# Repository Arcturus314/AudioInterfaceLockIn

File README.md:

A basic dual-phase lockin implementation for a 2in/2out sound card or audio interface using pyaudio. Tested on a MOTU M2 at 32bits/48kHz sample rate under ALSA.

Connect CH1 OUT to CH1 IN through a loopback wire and set gains appropriately. CH2 OUT should be the input to the DUT and CH2 IN should be the output of the DUT.

Example output file is `log_movemic.txt`. This was a simple experiment in which CH2 OUT was connected to a speaker, and CH2 IN connected to a microphone. The microphone was moved away from the speaker at a near-constant rate, and the resulting zero-crossings in the logfile occur when the reference signal and input are out of phase. The physical distance the microphone moves between zeroes provides the speed of sound.

Current problems: 
1. Processing loop is too slow for >48kHz
2. Generally unpolished
3. Move to sounddevice?

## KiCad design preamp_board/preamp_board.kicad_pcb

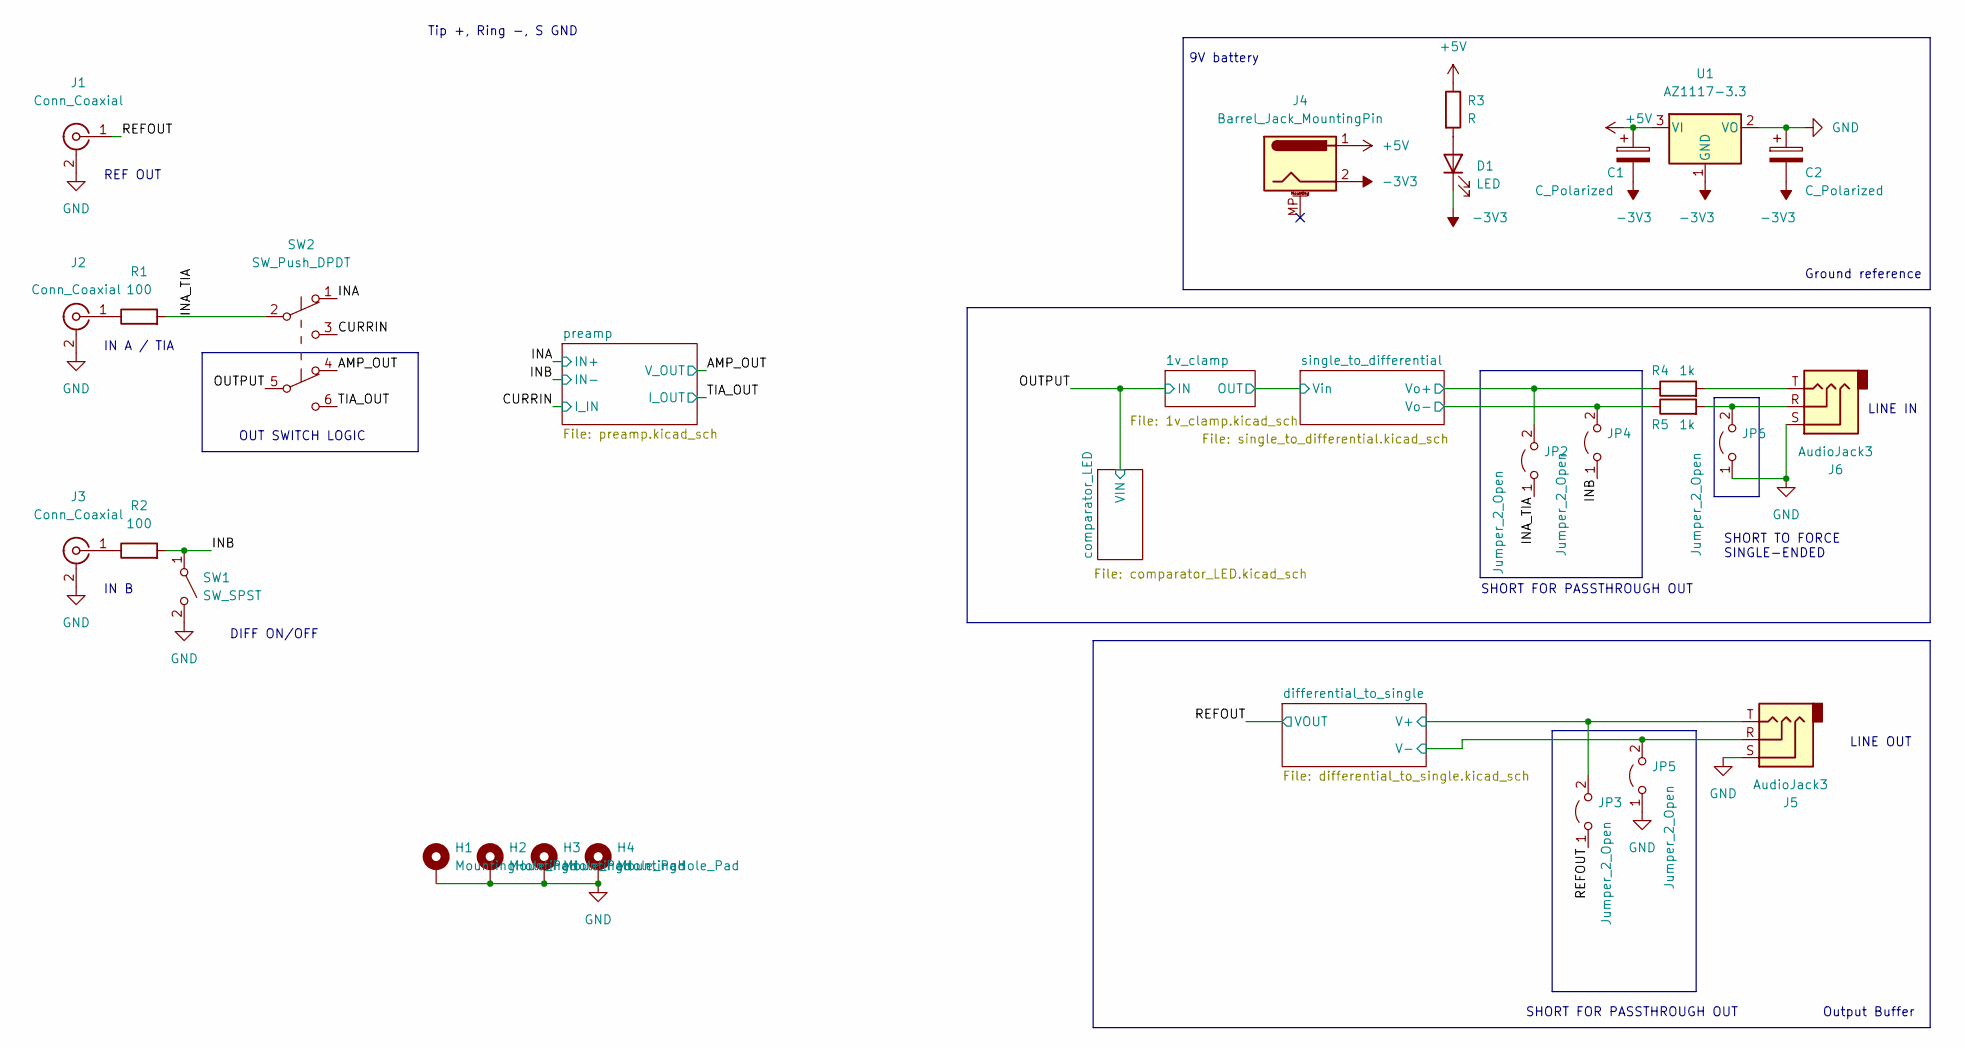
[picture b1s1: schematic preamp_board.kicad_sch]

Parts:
C1, C2: C_Polarized; CP_Radial_D5.0mm_P2.50mm
D1: LED; LED_0805_2012Metric_Pad1.15x1.40mm_HandSolder
H1, H2, H3, H4: MountingHole_Pad; MountingHole_3.2mm_M3_DIN965_Pad
J1, J2, J3: Conn_Coaxial; BNC_Amphenol_B6252HB-NPP3G-50_Horizontal
J4: Barrel_Jack_MountingPin; BarrelJack_CUI_PJ-063AH_Horizontal
J5, J6: AudioJack3; ACJS-MHDR
JP2, JP3, JP4, JP5, JP6: Jumper_2_Open; SolderJumper-2_P1.3mm_Open_TrianglePad1.0x1.5mm
R1, R2: 100; R_0805_2012Metric_Pad1.20x1.40mm_HandSolder
R3: R; R_0805_2012Metric_Pad1.20x1.40mm_HandSolder
R4, R5: 1k; R_0805_2012Metric_Pad1.20x1.40mm_HandSolder
SW1: SW_SPST; SW_E-Switch_EG1271_DPDT
SW2: SW_Push_DPDT; SW_E-Switch_EG1271_DPDT
U1: AZ1117-3.3; SOT-223-3_TabPin2

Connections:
+5V: C1.1, J4.1, R3.1, U1.3 (VI); also elsewhere on the board
-3V3: C1.2, C2.2, D1.1 (K), J4.2, U1.1 (GND); also elsewhere on the board
/AMP_OUT: SW2.4 (A); also elsewhere on the board
/CURRIN: SW2.3 (C); also elsewhere on the board
/INA: SW2.1 (A); also elsewhere on the board
/INA_TIA: JP2.1 (A), R1.2, SW2.2 (B)
/INB: JP4.1 (A), R2.2, SW1.1 (A); also elsewhere on the board
/OUTPUT: SW2.5 (B); also elsewhere on the board
/REFOUT: J1.1 (In), JP3.1 (A); also elsewhere on the board
/TIA_OUT: SW2.6 (C); also elsewhere on the board
/differential_to_single/V+: J5.T, JP3.2 (B); also elsewhere on the board
/differential_to_single/V-: J5.R, JP5.2 (B); also elsewhere on the board
/single_to_differential/Vo+: JP2.2 (B), R4.1; also elsewhere on the board
/single_to_differential/Vo-: JP4.2 (B), R5.1; also elsewhere on the board
GND: C2.1, H1.1, H2.1, H3.1, H4.1, J1.2 (Ext), J2.2 (Ext), J3.2 (Ext), J5.S, J6.S, JP5.1 (A), JP6.1 (A), SW1.2 (B), U1.2 (VO); also elsewhere on the board
unnamed: D1.2 (A), R3.2
unnamed: J2.1 (In), R1.1
unnamed: J3.1 (In), R2.1
unnamed: J6.R, JP6.2 (B), R5.2
unnamed: J6.T, R4.2

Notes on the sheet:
REF OUT
9V battery
IN B
SHORT FOR PASSTHROUGH OUT
IN A / TIA
DIFF ON/OFF
LINE OUT
Output Buffer
Tip +, Ring -, S GND
SHORT TO FORCE SINGLE-ENDED
LINE IN
Ground reference
OUT SWITCH LOGIC

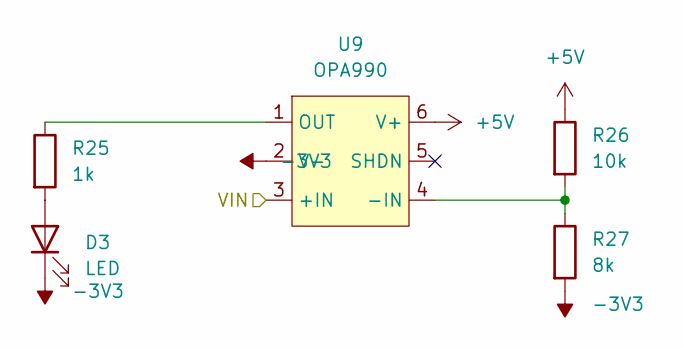
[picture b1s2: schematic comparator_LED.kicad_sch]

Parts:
D3: LED; LED_D3.0mm
R25: 1k; R_0805_2012Metric_Pad1.20x1.40mm_HandSolder
R26: 10k; R_0805_2012Metric_Pad1.20x1.40mm_HandSolder
R27: 8k; R_0805_2012Metric_Pad1.20x1.40mm_HandSolder
U9: OPA990; SOT-23-6_Handsoldering

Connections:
+5V: R26.1, U9.6 (V+); also elsewhere on the board
-3V3: D3.1 (K), R27.2, U9.2 (V-); also elsewhere on the board
/OUTPUT: U9.3 (+IN); also elsewhere on the board
unnamed: D3.2 (A), R25.2
unnamed: R25.1, U9.1 (OUT)
unnamed: R26.2, R27.1, U9.4 (-IN)

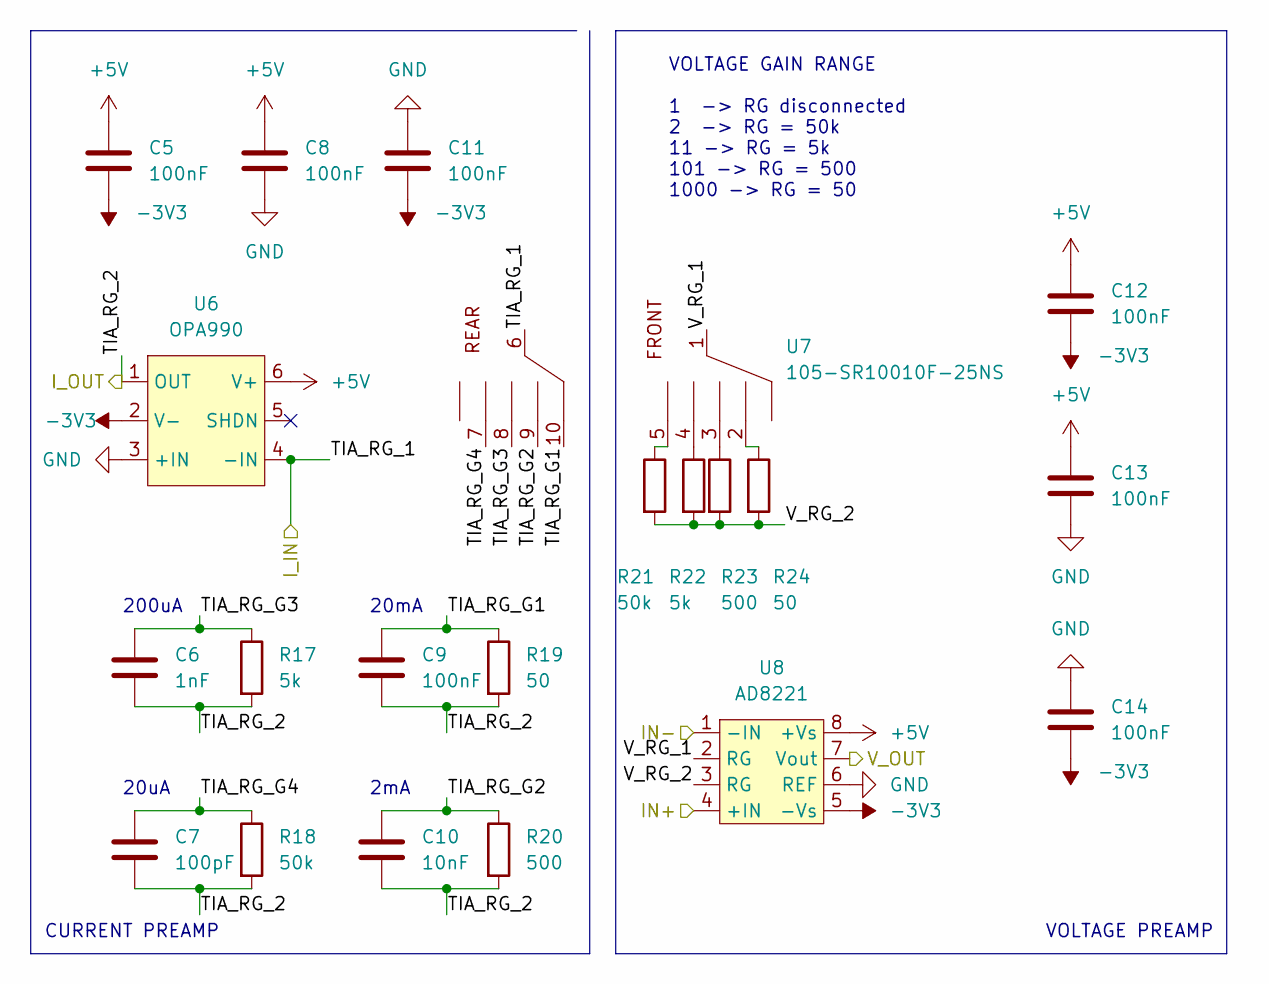
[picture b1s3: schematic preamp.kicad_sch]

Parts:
C5, C8, C9, C11, C12, C13, C14: 100nF; C_0805_2012Metric_Pad1.18x1.45mm_HandSolder
C6: 1nF; C_0805_2012Metric_Pad1.18x1.45mm_HandSolder
C7: 100pF; C_0805_2012Metric_Pad1.18x1.45mm_HandSolder
C10: 10nF; C_0805_2012Metric_Pad1.18x1.45mm_HandSolder
R17, R22: 5k; R_0805_2012Metric_Pad1.20x1.40mm_HandSolder
R18, R21: 50k; R_0805_2012Metric_Pad1.20x1.40mm_HandSolder
R19, R24: 50; R_0805_2012Metric_Pad1.20x1.40mm_HandSolder
R20, R23: 500; R_0805_2012Metric_Pad1.20x1.40mm_HandSolder
U6: OPA990; SOT-23-6_Handsoldering
U7: 105-SR10010F-25NS
U8: AD8221; MSOP-8_3x3mm_P0.65mm

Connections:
+5V: C5.1, C8.1, C12.1, C13.1, U6.6 (V+), U8.8 (+Vs); also elsewhere on the board
-3V3: C5.2, C11.2, C12.2, C14.2, U6.2 (V-), U8.5 (-Vs); also elsewhere on the board
/AMP_OUT: U8.7 (Vout); also elsewhere on the board
/CURRIN: U6.4 (-IN), U7.6; also elsewhere on the board
/INA: U8.4 (+IN); also elsewhere on the board
/INB: U8.1 (-IN); also elsewhere on the board
/TIA_OUT: C6.2, C7.2, C9.2, C10.2, R17.2, R18.2, R19.2, R20.2, U6.1 (OUT); also elsewhere on the board
/preamp/TIA_RG_G1: C9.1, R19.1, U7.10
/preamp/TIA_RG_G2: C10.1, R20.1, U7.9
/preamp/TIA_RG_G3: C6.1, R17.1, U7.8
/preamp/TIA_RG_G4: C7.1, R18.1, U7.7
/preamp/V_RG_1: U7.1, U8.2 (RG)
/preamp/V_RG_2: R21.2, R22.2, R23.2, R24.2, U8.3 (RG)
GND: C8.2, C11.1, C13.2, C14.1, U6.3 (+IN), U8.6 (REF); also elsewhere on the board
unnamed: R21.1, U7.5
unnamed: R22.1, U7.4
unnamed: R23.1, U7.3
unnamed: R24.1, U7.2

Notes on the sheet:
200uA
2mA
20mA
VOLTAGE PREAMP
20uA
VOLTAGE GAIN RANGE 1 -> RG disconnected 2 -> RG = 50k 11 -> RG = 5k 101 -> RG = 500 1000 -> RG = 50
CURRENT PREAMP

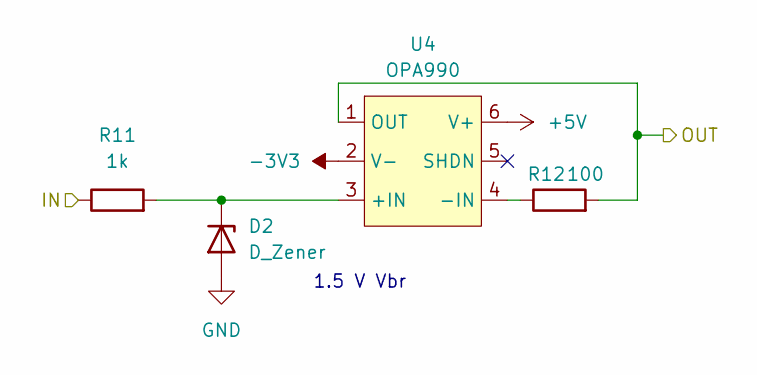
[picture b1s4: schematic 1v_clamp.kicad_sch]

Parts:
D2: D_Zener; D_SOD-323_HandSoldering
R11: 1k; R_0805_2012Metric_Pad1.20x1.40mm_HandSolder
R12: 100; R_0805_2012Metric_Pad1.20x1.40mm_HandSolder
U4: OPA990; SOT-23-6_Handsoldering

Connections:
+5V: U4.6 (V+); also elsewhere on the board
-3V3: U4.2 (V-); also elsewhere on the board
/1v_clamp/OUT: R12.2, U4.1 (OUT); also elsewhere on the board
/OUTPUT: R11.1; also elsewhere on the board
GND: D2.2 (A); also elsewhere on the board
unnamed: D2.1 (K), R11.2, U4.3 (+IN)
unnamed: R12.1, U4.4 (-IN)

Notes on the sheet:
1.5 V Vbr

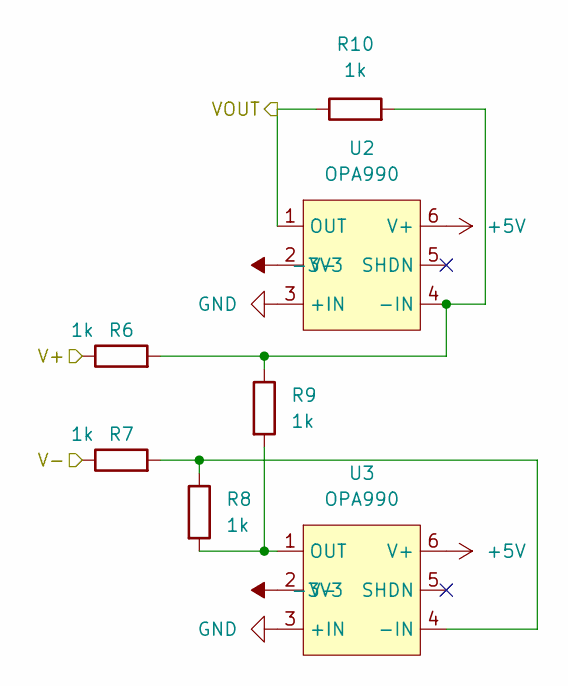
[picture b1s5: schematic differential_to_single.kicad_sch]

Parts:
R6, R7, R8, R9, R10: 1k; R_0805_2012Metric_Pad1.20x1.40mm_HandSolder
U2, U3: OPA990; SOT-23-6_Handsoldering

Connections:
+5V: U2.6 (V+), U3.6 (V+); also elsewhere on the board
-3V3: U2.2 (V-), U3.2 (V-); also elsewhere on the board
/REFOUT: R10.1, U2.1 (OUT); also elsewhere on the board
/differential_to_single/V+: R6.1; also elsewhere on the board
/differential_to_single/V-: R7.1; also elsewhere on the board
GND: U2.3 (+IN), U3.3 (+IN); also elsewhere on the board
unnamed: R7.2, R8.1, U3.4 (-IN)
unnamed: R8.2, R9.2, U3.1 (OUT)
unnamed: R6.2, R9.1, R10.2, U2.4 (-IN)

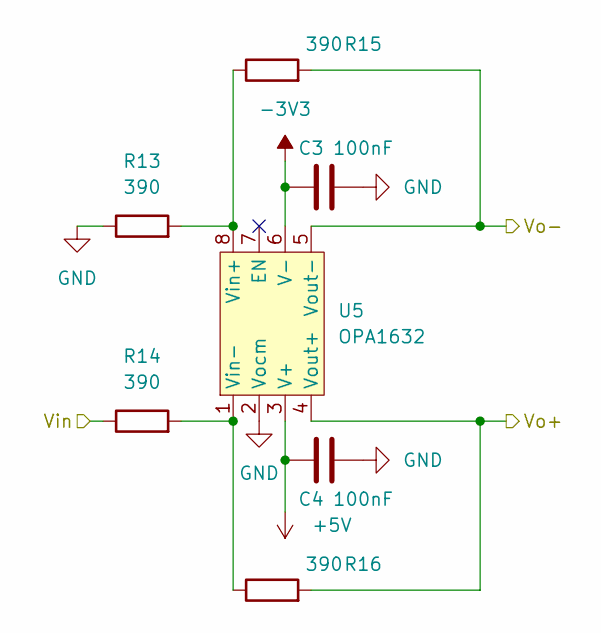
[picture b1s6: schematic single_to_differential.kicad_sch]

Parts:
C3, C4: 100nF; C_0805_2012Metric_Pad1.18x1.45mm_HandSolder
R13, R14, R15, R16: 390; R_0805_2012Metric_Pad1.20x1.40mm_HandSolder
U5: OPA1632; SOIC-8_3.9x4.9mm_P1.27mm

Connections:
+5V: C4.1, U5.3 (V+); also elsewhere on the board
-3V3: C3.1, U5.6 (V-); also elsewhere on the board
/1v_clamp/OUT: R14.1; also elsewhere on the board
/single_to_differential/Vo+: R16.2, U5.4 (Vout+); also elsewhere on the board
/single_to_differential/Vo-: R15.2, U5.5 (Vout-); also elsewhere on the board
GND: C3.2, C4.2, R13.1, U5.2 (Vocm); also elsewhere on the board
unnamed: R13.2, R15.1, U5.8 (Vin+)
unnamed: R14.2, R16.1, U5.1 (Vin-)

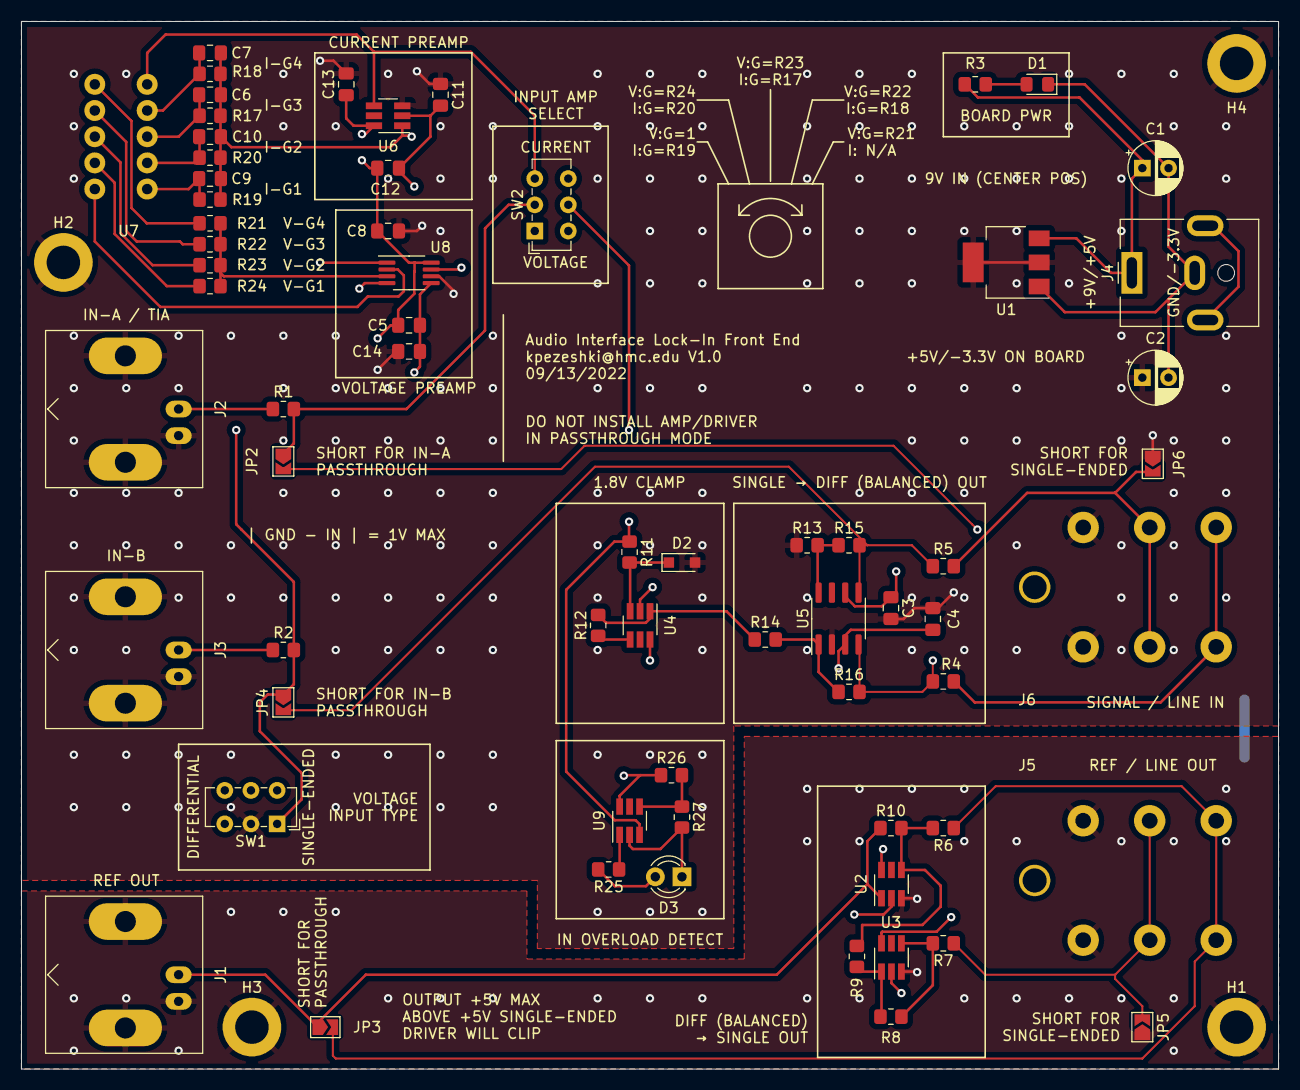
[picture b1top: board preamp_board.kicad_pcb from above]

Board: 4 copper layers, 120.0 x 100.0 mm, 70 parts (0 on the bottom side), 41 nets.

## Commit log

2022-09-11 initial V1.0 commit
2022-09-11 added picture
2022-09-13 Added preamplifier PCB design (untested)
